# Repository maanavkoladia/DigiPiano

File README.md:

# DigiPiano

The **DigiPiano** is a velocity-sensitive digital piano designed using **STM32** and **ESP32** microcontrollers. It combines advanced sensor technology, high-quality audio playback, and Bluetooth connectivity to deliver a realistic and modern musical experience.

## Project Overview

- **Key Tracking Mechanism:**
  - Uses **Hall effect sensors** and magnets to detect key presses and releases.
  - Tracks key velocity to simulate the dynamics of a real piano.

- **Audio Playback:**
  - Plays pre-recorded piano note samples stored in external memory.
  - Outputs sound via AUX to speakers or streams wirelessly over Bluetooth.

- **Custom Sustain Circuitry:**
  - Includes a custom-designed sustain circuit to enhance the playing experience.

- **Communication Between Microcontrollers:**
  - The STM32 and ESP32 communicate efficiently using **SPI** and **UART** protocols, enabling seamless data exchange for key detection and audio output.

## Implementation Highlights

- The firmware handles multichannel analog data acquisition and processes it to detect key strokes with precision.
- Audio playback is managed through external memory, ensuring low-latency performance.
- Bluetooth functionality allows for wireless connectivity, enabling modern use cases such as streaming to Bluetooth speakers or devices.
- The hardware design incorporates a custom PCB layout for compactness and reliability, integrating sensors, microcontrollers, and audio components.

## See It in Action

Check out this [Instagram reel](https://www.instagram.com/reel/DDNmyurpquJ/?igsh=Y2NvNWVrb3MxazM1) to see the DigiPiano in action!

The DigiPiano is a versatile and user-friendly project, blending traditional piano functionality with modern digital and IoT capabilities.

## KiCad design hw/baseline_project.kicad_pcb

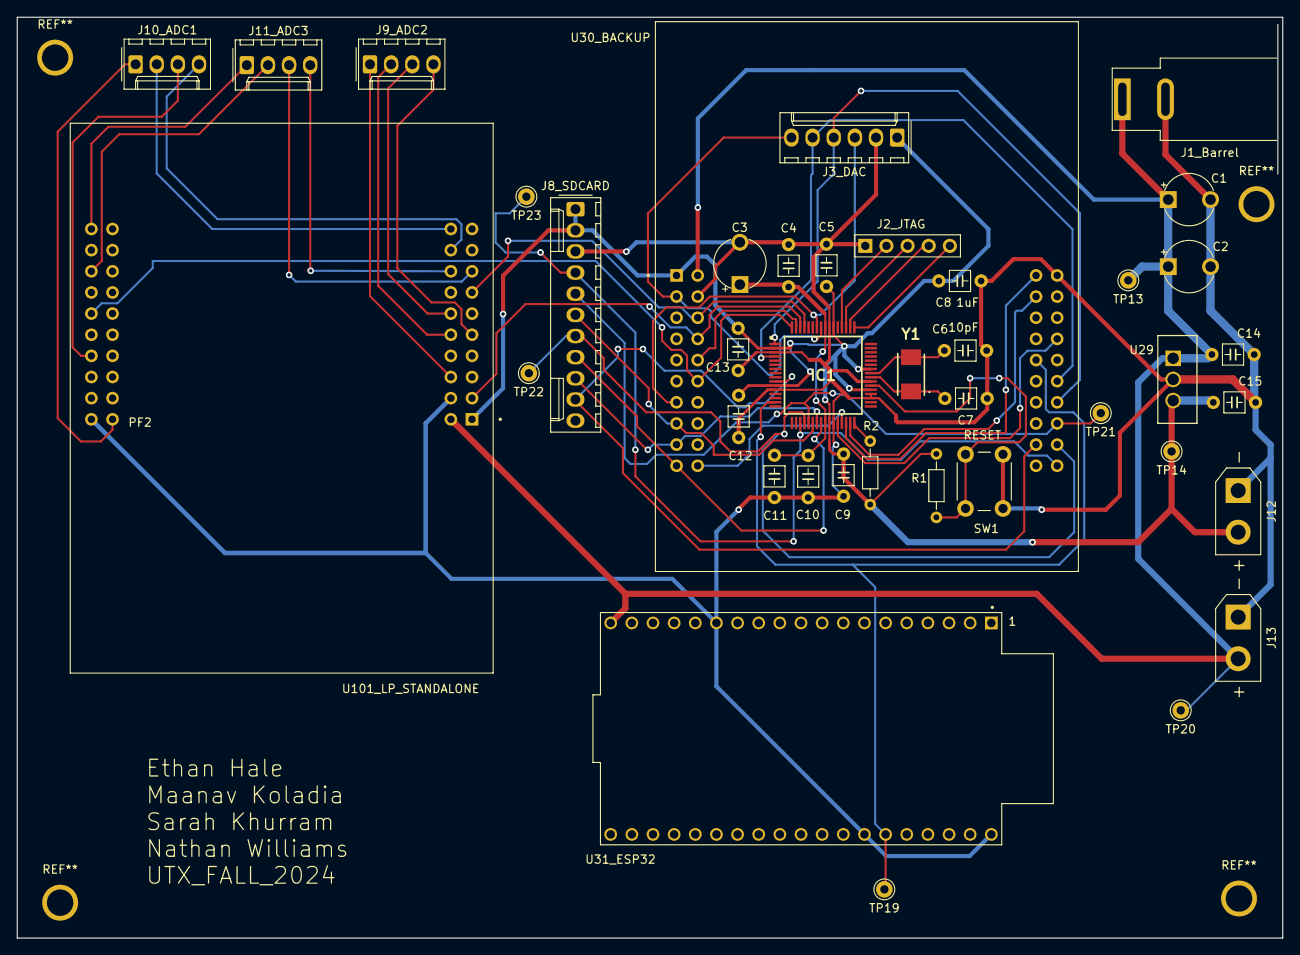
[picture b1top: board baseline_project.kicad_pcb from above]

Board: 2 copper layers, 152.0 x 110.6 mm, 40 parts (0 on the bottom side), 44 nets.

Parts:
C1, C2: 1uF; CP_Radial_Tantal200mil
C3: 2.2uF; CP_Radial_Tantal200mil
C4, C5, C10, C12, C14: 0.1uF; C_Axial_200mil
C6, C7: 10pF; C_Axial_200mil
C8, C11: 1uF; C_Axial_200mil
C9, C13: 0.01uF; C_Axial_200mil
C15: 10uF; C_Axial_200mil
IC1: TM4C123GH6PMIR; QFP50P1200X1200X160-64N
J1_Barrel: Barrel_Jack; BarrelJack_SwitchcraftConxall_RAPC10U_Horizontal
J2_JTAG: Header_5; PinHeader_1x05_P2.54mm_Vertical
J3_DAC: Conn_01x06_Socket_DAC; Molex_KK-254_AE-6410-06A_1x06_P2.54mm_Vertical
J8_SDCARD: LCD SD HEADERS; Molex_KK-254_AE-6410-11A_1x11_P2.54mm_Vertical
J9_ADC2: ADC2; Molex_KK-254_AE-6410-04A_1x04_P2.54mm_Vertical
J10_ADC1: ADC1; Molex_KK-254_AE-6410-04A_1x04_P2.54mm_Vertical
J11_ADC3: ADC3; Molex_KK-254_AE-6410-04A_1x04_P2.54mm_Vertical
J12: 3.3V Pads; AMASS_XT30UPB-M_1x02_P5.0mm_Vertical
J13: 5V Pads; AMASS_XT30UPB-M_1x02_P5.0mm_Vertical
R1: 10k; R_Axial_DIN0204_L3.6mm_D1.6mm_P7.62mm_Horizontal
R2: 1M; R_Axial_DIN0204_L3.6mm_D1.6mm_P7.62mm_Horizontal
SW1: RESET; SW_PUSH_6mm
TP13, TP14, TP19, TP20, TP21, TP22, TP23: TestPoint; Pin_D1.0mm_L10.0mm
U29: LM2937ET-3.3/NOPB; T03B
U30_BACKUP, U101_LP_STANDALONE: EK-TM4C123GXL; ti_EKTM4C123GXL
U31_ESP32: ESP32-DEVKITC; MODULE_ESP32-DEVKITC
Y1: ABM3-16.000MHZ-B2-T; ABM3

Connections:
+3V3: C5.1, C8.1, C9.1, C12.1, C13.1, C15.1, IC1.2 (VDDA), IC1.11 (VDD_1), IC1.26 (VDD_2), IC1.37 (VBAT), IC1.42 (VDD_3), IC1.54 (VDD_4), J3_DAC.1, J8_SDCARD.1, J8_SDCARD.2, J12.2, R1.1, R2.1, TP14.1, U29.3 (OUT), U30_BACKUP.J1_1 (+3.3V), U101_LP_STANDALONE.J1_1 (+3.3V)
+5V: C1.1, C2.1, C14.1, J1_Barrel.1, J13.2, TP13.1, TP20.1, U29.1 (IN), U30_BACKUP.J3_1 (+VBUS), U31_ESP32.19 (EXT_5V), U101_LP_STANDALONE.J3_1 (+VBUS)
/LD0: C3.1, C4.1, C10.1, C11.1, IC1.25 (VDDC_1), IC1.56 (VDDC_2)
GND: C1.2, C2.2, C3.2, C4.2, C5.2, C6.2, C7.1, C8.2, C9.2, C10.2, C11.2, C12.2, C13.2, C14.2, C15.2, IC1.3 (GNDA), IC1.12 (GND_1), IC1.27 (GND_2), IC1.35 (GNDX), IC1.36 (XOSC1), IC1.39 (GND_3), IC1.55 (GND_4), J1_Barrel.2, J2_JTAG.1 (A), J3_DAC.2, J8_SDCARD.3, J12.1, J13.1, SW1.1, U29.2 (GND), U30_BACKUP.J2_1 (GND), U30_BACKUP.J3_2 (GND), U31_ESP32.14 (GND1), U31_ESP32.32 (GND2), U31_ESP32.38 (GND3), U101_LP_STANDALONE.J2_1 (GND), U101_LP_STANDALONE.J3_2 (GND)
IO21: IC1.15 (PC5), TP19.1, U30_BACKUP.J4_5 (PC5), U31_ESP32.33 (IO21)
LP_PA2: J11_ADC3.1, U101_LP_STANDALONE.J2_10 (PA2)
LP_PA4: J11_ADC3.2, U101_LP_STANDALONE.J2_8 (PA4)
LP_PA5: J11_ADC3.3, U101_LP_STANDALONE.J1_8 (PA5)
LP_PB4: IC1.61 (PD0), U30_BACKUP.J3_3 (PD0), U101_LP_STANDALONE.J1_7 (PB4)
LP_PB5: IC1.62 (PD1), U30_BACKUP.J3_4 (PD1), U101_LP_STANDALONE.J1_2 (PB5)
LP_PB7: IC1.64 (PD3), U30_BACKUP.J3_6 (PD3), U101_LP_STANDALONE.J2_6 (PB7)
LP_PD0: J9_ADC2.1, U101_LP_STANDALONE.J3_3 (PD0)
LP_PD2: J9_ADC2.2, U101_LP_STANDALONE.J3_5 (PD2)
LP_PD3: J9_ADC2.3, U101_LP_STANDALONE.J3_6 (PD3)
LP_PE2: J11_ADC3.4, U101_LP_STANDALONE.J3_8 (PE2)
LP_PE3: J10_ADC1.4, U101_LP_STANDALONE.J3_9 (PE3)
LP_PE4: J9_ADC2.4, U101_LP_STANDALONE.J1_5 (PE4)
LP_PF0: J10_ADC1.3, U101_LP_STANDALONE.J2_4 (PF0)
LP_PF1: J10_ADC1.2, U101_LP_STANDALONE.J3_10 (PF1)
LP_PF2: J10_ADC1.1, U101_LP_STANDALONE.J4_1 (PF2)
unnamed: C7.2, IC1.40 (OSC0), Y1.1
unnamed: C6.1, IC1.41 (OSC1), Y1.2
unnamed: IC1.52 (PC0/TCK/SWCLK), J2_JTAG.2 (B)
unnamed: IC1.51 (PC1/TMS/SWDIO), J2_JTAG.3 (C)
unnamed: IC1.50 (PC2/TDI), J2_JTAG.4 (C)
unnamed: IC1.49 (PC3/TDO/SWO), J2_JTAG.5 (C)
unnamed: IC1.38 (~RST), R1.2, SW1.2
unnamed: IC1.32 (~WAKE), R2.2
TM_PA2: IC1.19 (PA2/SSI0C1K), J8_SDCARD.4, TP23.1, U30_BACKUP.J2_10 (PA2)
TM_PA3: IC1.20 (PA3/SSI0FSS), J8_SDCARD.7, TP22.1, U30_BACKUP.J2_9 (PA3)
TM_PA4: IC1.21 (PA4/SSI0RX), J8_SDCARD.5, TP21.1, U30_BACKUP.J2_8 (PA4)
TM_PA5: IC1.22 (PA5/SSI0TX), J8_SDCARD.6, U30_BACKUP.J1_8 (PA5)
TM_PA6: IC1.23 (PA6), J8_SDCARD.9, U30_BACKUP.J1_9 (PA6)
TM_PA7: IC1.24 (PA7), J8_SDCARD.8, U30_BACKUP.J1_10 (PA7)
TM_PB4: IC1.58 (PB4), J3_DAC.3, U30_BACKUP.J1_7 (PB4)
TM_PB5: IC1.57 (PB5), J3_DAC.6, U30_BACKUP.J1_2 (PB5)
TM_PB6: IC1.1 (PB6), J3_DAC.4, U30_BACKUP.J2_7 (PB6)
TM_PB7: IC1.4 (PB7), J3_DAC.5, U30_BACKUP.J2_6 (PB7)
TM_PD2: IC1.63 (PD2), U30_BACKUP.J3_5 (PD2)
TM_PD7: IC1.10 (PD7), J8_SDCARD.10, U30_BACKUP.J4_9 (PD7)
TM_PF0: IC1.28 (PF0), U30_BACKUP.J2_4 (PF0)
TM_PF1: IC1.29 (PF1), U30_BACKUP.J3_10 (PF1)
TM_PF2: IC1.30 (PF2), U30_BACKUP.J4_1 (PF2)
TM_PF3: IC1.31 (PF3), U30_BACKUP.J4_2 (PF3)

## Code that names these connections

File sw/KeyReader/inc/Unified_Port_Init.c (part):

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// Port A drives the ST7735 LCD 
//
// Backlight (pin 10) connected to +3.3 V
// MISO      (pin 9)  connected to PA4
// SCK       (pin 8)  connected to PA2 (SSI0Clk)
// MOSI      (pin 7)  connected to PA5 (SSI0Tx)
// TFT_CS    (pin 6)  connected to PA3 (SSI0Fss)
// CARD_CS   (pin 5)  connected to PB0 (GPIO)
// Data/CMD  (pin 4)  connected to PA6 (GPIO), high for data, low for command
// RESET     (pin 3)  connected to PA7 (GPIO)
// VCC       (pin 2)  connected to +3.3 V
// Gnd       (pin 1)  connected to ground
//
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  SYSCTL_RCGCGPIO_R     |= 0x01;            // Activate port A
  while((SYSCTL_PRGPIO_R & 0x01)==0){};     // allow time for clock to start
    
  GPIO_PORTA_DIR_R      |= 0xC8;            // make PA3,6,7 out
  GPIO_PORTA_AFSEL_R    &= ~0xC8;           // disable alt funct on PA3,6,7
  GPIO_PORTA_DEN_R      |= 0xC8;            // enable digital I/O on PA3,6,7
  
  // configure PA3,6,7 as GPIO
  GPIO_PORTA_PCTL_R      = (GPIO_PORTA_PCTL_R
                         & 0x00FF0FFF)
                         + 0x00000000;
  
  GPIO_PORTA_AMSEL_R    &= ~0xC8;           // disable analog functionality on PA3,6,7

  // initialize SSI0
  GPIO_PORTA_AFSEL_R    |= 0x2C;            // enable alt funct on PA2,3,5
  GPIO_PORTA_DEN_R      |= 0x2C;            // enable digital I/O on PA2,3,5
 
  // configure PA2,3,5 as SSI
  GPIO_PORTA_PCTL_R      = (GPIO_PORTA_PCTL_R
                         & 0xFF0F00FF)
                         + 0x00202200;
  
  GPIO_PORTA_AMSEL_R    &= ~0x2C;           // disable analog functionality on PA2,3,5
  SSI0_CR1_R            &= ~SSI_CR1_SSE;    // disable SSI
  SSI0_CR1_R            &= ~SSI_CR1_MS;     // master mode
  
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// ----------------    PORT B Initialization   --------------------------------
// ----------------------------------------------------------------------------
//
// PB7 = PWM Ouptut to JP6 (M0PWM1)
// PB6 = PWM Output to Motor (M0PWM0)
// PB5 = ADC Input (AIN11)
// PB4 = Timer Capture input (T1CCP0)
// PB3 = GPIO 
// PB2 = GPIO/I2C0
// PB1 = GPIO/I2C0CL
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  SYSCTL_RCGCGPIO_R     |= 0x02;            // activate port B
  while((SYSCTL_PRGPIO_R & 0x02) == 0){};   // Wait
  
  // ---------------  Initialize PB7 as M0PWM1  -----------------------  

  GPIO_PORTB_AFSEL_R    |=  0x80;           // enable alt funct on PB7
  GPIO_PORTB_PCTL_R     &= ~0xF0000000;     // configure PB7 as M0PWM1
  GPIO_PORTB_PCTL_R     |=  0x40000000;
  GPIO_PORTB_AMSEL_R    &= ~0x80;           // disable analog functionality on PB7
  GPIO_PORTB_DEN_R      |=  0x80;           // enable digital I/O on PB7

  // ---------------  Initialize PB6 as M0PWM0  -----------------------
  GPIO_PORTB_AFSEL_R    |=  0x40;           // enable alt funct on PB6
  GPIO_PORTB_PCTL_R     &= ~0x0F000000;     // configure PB6 as PWM0
  GPIO_PORTB_PCTL_R     |=  0x04000000;  
  GPIO_PORTB_AMSEL_R    &= ~0x40;           // disable analog functionality on PB6
  GPIO_PORTB_DEN_R      |=  0x40;           // enable digital I/O on PB6
  
  // ---------------  Initialize PB5 as AIN11  ----------------------- 
  GPIO_PORTB_DIR_R      &= ~0x20;           // make PB5 input
  GPIO_PORTB_AFSEL_R    |=  0x20;           // enable alternate function on PB5
  GPIO_PORTB_DEN_R      &= ~0x20;           // disable digital I/O on PB5
  GPIO_PORTB_AMSEL_R    |=  0x20;           // enable analog functionality on PB5

  // ----------------- Initialize PB4 as Timer Capture input (T1CCP0) ---------
  GPIO_PORTB_DIR_R      &= ~0x10;           // make PB4 input
  GPIO_PORTB_AFSEL_R    |= 0x10;            // enable alt funct on PB4
  GPIO_PORTB_DEN_R      |= 0x10;            // enable digital I/O on PB4
                                            // configure PB4 (T1CCP0)
  GPIO_PORTB_PCTL_R     = (GPIO_PORTB_PCTL_R 
                        &  0xFFF0FFFF)
                        +  0x00070000;
  GPIO_PORTB_AMSEL_R    &= ~0x10;           // disable analog functionality on PB4

  // ----------------- Initialize PB3-0 as GPIO ---------
                                      
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// ----------------------------------------------------------------------------
//
// PC4 = UP switch
// PC5 = RIGHT switch
// PC6 = LEFT switch
// PC7 = DOWN switch
//
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// ----------------    PORT D Initialization   --------------------------------
// ----------------------------------------------------------------------------
//
// PD7 = U2TX
// PD6 = U2RX
// PD3 = SSI1_MOSI  (to TLV5616)
// PD2 = AIN5 (Monitor DAC_OUT signal from TLV5616)
// PD1 = SSI1_FS/CS (to TLV5616)
// PD0 = SSI1_SCK   (to TLV5616)
  
void Port_D_Init(void){
 
  SYSCTL_RCGCGPIO_R     |= 0x08;            // activate port D
  while((SYSCTL_PRGPIO_R & 0x08)==0){};     // allow time for clock to stabilize

  // ---------------  Initialize PB7 as U2TX, PB6 as U2RX  -----------------------  
    
  GPIO_PORTD_LOCK_R      = 0x4C4F434B;      // unlock REQUIRED for PD7
  GPIO_PORTD_CR_R       |= 0xC0;            // commit PD6, PD7
  
  GPIO_PORTD_AMSEL_R    &= ~0xC0;           // disable analog functionality on PD6, PD7
  GPIO_PORTD_AFSEL_R    |=  0xC0;           // enable alternate function on PD6, PD7
  GPIO_PORTD_DEN_R      |=  0xC0;           // enable digital on PD6, PD7 (PD6 is U2RX, PD7 is U2TX)
  GPIO_PORTD_PCTL_R      =(GPIO_PORTD_PCTL_R  
                         & 0x00FFFFFF)
                         | 0x11000000;      // configure PD6, PD7 as UART
 
   // ---------------  Initialize PD2 as AIN5  ----------------------------------  
   
  GPIO_PORTD_DIR_R      &= ~0x04;           // make PD2 input
  GPIO_PORTD_AFSEL_R    |=  0x04;           // enable alternate function on PD2
  GPIO_PORTD_DEN_R      &= ~0x04;           // disable digital I/O on PD2
  GPIO_PORTD_AMSEL_R    |=  0x04;           // enable analog functionality on PD2

  // ---------------  Initialize PD3,1,0 as SSI1 MOSI, FS & SCK  ---------------- 
    
  GPIO_PORTD_AMSEL_R    &= ~0x0B;           // disable analog functionality on PD
  GPIO_PORTD_AFSEL_R    |=  0x0B;           // enable alt funct on PD3,1,0
  GPIO_PORTD_DEN_R      |=  0x0B;           // enable digital I/O on PD3,1,0
  GPIO_PORTD_PCTL_R      = (GPIO_PORTD_PCTL_R
                          & 0xFFFF0F00)
                          + 0x00002022;
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// ----------------------------------------------------------------------------
//
// PE5 = U5TX
// PE4 = U5RX
// PE3 = Heartbeat LED
// PE2 = AIN_1 (DAC_OUT Monitor)
// PE1 = RSTB_8266
// PE0 = 8266_ GPIO_2 

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  SYSCTL_RCGCGPIO_R     |= 0x10;            // activate port E
  while((SYSCTL_PRGPIO_R & 0x10)==0){};

 // ---------------  Initialize PE5 as U5TX, PE4 as U5RX  -----------------------  

  GPIO_PORTE_AFSEL_R    |= 0x30;            // enable alt funct on PE5-4
  GPIO_PORTE_DEN_R      |= 0x30;            // enable digital I/O on PE5-4
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                         + 0x00110000;
  GPIO_PORTE_AMSEL_R    &= ~0x30;           // disable analog functionality on PE

 // ---------------  Initialize PE3,1,0 as GPIO  ---------------------------------  

  GPIO_PORTE_DIR_R      |=  0x0A;           // output digital I/O on PE3,1
  GPIO_PORTE_DIR_R      &= ~0x01;           // input digital I/O on PE0
  GPIO_PORTE_AMSEL_R    &= ~0x0B;           // disable analog functionality on PE3,1,0
  GPIO_PORTE_AFSEL_R    &= ~0x0B;           // disable alt funct on PE3,1,0
  GPIO_PORTE_DEN_R      |=  0x0B;           // enable digital I/O on PE3,1,0
  
  GPIO_PORTE_PCTL_R      = (GPIO_PORTE_PCTL_R 
                         & 0xFFFF0F00);
  
// ---------------  Initialize PE2 as AIN1  ---------------------------------  
  
  GPIO_PORTE_DIR_R      &= ~0x04;           // make PE2 input
  GPIO_PORTE_AFSEL_R    |=  0x04;           // enable alternate function on PE2
  GPIO_PORTE_DEN_R      &= ~0x04;           // disable digital I/O on PE2
  GPIO_PORTE_AMSEL_R    |=  0x04;           // enable analog functionality on PE2
}
  
// ----------------------------------------------------------------------------
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  
  GPIO_PORTF_AMSEL_R    = 0x00;             // disable analog on PF
  GPIO_PORTF_PCTL_R     = 0x00000000;       // PCTL GPIO on PF4-0
  GPIO_PORTF_DIR_R      = 0x0E;             // PF4,PF0 in, PF3-1 out
  GPIO_PORTF_AFSEL_R    = 0x00;             // disable alt funct on PF7-0
  GPIO_PORTF_PUR_R      = 0x11;             // enable pull-up on PF0 and PF4
  GPIO_PORTF_DEN_R      = 0x1F;             // enable digital I/O on PF4-0
}

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
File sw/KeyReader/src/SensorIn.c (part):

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void ADC_IC_Init(void) {
    // Enable SSI0, SSI2, SSI3

    // ---- Configure Port A for SSI0 (PA2-PA5) ----
    // PA2 = SSI0Clk (Clock)
    // PA3 = SSI0Fss (Chip Select/Frame Select, used pe2 instead
    // PA4 = SSI0Rx  (MISO, Master In Slave Out)
    // PA5 = SSI0Tx  (MOSI, Master Out Slave In)

    // ---- Configure Port B for SSI2 (PB4-PB7) ----
    // PB4 = SSI2Clk (Clock)
    // PB5 = SSI2Fss (Chip Select/Frame Select), used pe3 instead
    // PB6 = SSI2Rx  (MISO, Master In Slave Out)
    // PB7 = SSI2Tx  (MOSI, Master Out Slave In)

    // ---- Configure Port D for SSI3 (PD0-PD3) ----
    // PD0 = SSI3Clk (Clock)
    // PD1 = SSI3Fss (Chip Select/Frame Select), using pe4 instead
    // PD2 = SSI3Rx  (MISO, Master In Slave Out)
    // PD3 = SSI3Tx  (MOSI, Master Out Slave In)
    // Enable SSI0, SSI1, SSI2
    SYSCTL_RCGCSSI_R |= (SYSCTL_RCGCSSI_R0 | SYSCTL_RCGCSSI_R2 | SYSCTL_RCGCSSI_R3);  // Enable SSI0, SSI2, and SSI3
    while((SYSCTL_PRSSI_R & (SYSCTL_RCGCSSI_R0 | SYSCTL_RCGCSSI_R2 | SYSCTL_RCGCSSI_R3)) == 0) {}  // Wait until SSI0, SSI2, and SSI3 are ready
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    SYSCTL_RCGCGPIO_R |= (SYSCTL_RCGCGPIO_R0 | SYSCTL_RCGCGPIO_R1 | SYSCTL_RCGCGPIO_R3);  // Enable clocks for Port A, B, D
    while((SYSCTL_PRGPIO_R & (SYSCTL_RCGCGPIO_R0 | SYSCTL_RCGCGPIO_R1 | SYSCTL_RCGCGPIO_R3)) == 0) {}  // Wait until Ports A, B, D are ready

    // ---- Configure Port A for SSI0 (PA2-PA5) ----
    GPIO_PORTA_AFSEL_R |= 0x3C;                    // Enable alt funct on PA2-PA5 
    GPIO_PORTA_DEN_R |= 0x3C;                      // Enable digital I/O on PA2-PA5
    GPIO_PORTA_PCTL_R = (GPIO_PORTA_PCTL_R & 0xFF0000FF) + 0x00222200; // Configure PA2-PA5 as SSI
    GPIO_PORTA_AMSEL_R &= ~0x3C;                  // Disable analog functionality on PA2-PA5
    GPIO_PORTA_DIR_R |= 0x2C;  //make pa2,3,5 out
    GPIO_PORTA_DIR_R &= ~0x10;  //make pa4 in

    // ---- Configure Port B for SSI2 (PB4-PB7) ----
    GPIO_PORTB_AFSEL_R |= 0xF0;                    // Enable alt funct on PB4-PB7
    GPIO_PORTB_DEN_R |= 0xF0;                      // Enable digital I/O on PB4-PB7
    GPIO_PORTB_PCTL_R = (GPIO_PORTB_PCTL_R & 0x0000FFFF) + 0x22220000; // Configure PB4-PB7 as SSI
    GPIO_PORTB_AMSEL_R &= ~0xF0;                   // Disable analog functionality on PB4-PB7
    GPIO_PORTB_DIR_R |= 0xB0;  //make pb 7,5,4 out 11X1XXX
    GPIO_PORTB_DIR_R &= ~0x40;  //make pb6 in   XX0XXXXX
    //GPIO_PORTB_PDR_R |= 0x80;  // Enable pull-down on PB7


    // Set PB7 (SPI2 MOSI) to 8mA drive strength
    //GPIO_PORTB_DR8R_R |= 0x80;  // 0x80 = 0b10000000, enables 8mA drive on PB7


    // ---- Configure Port D for SSI3 (PD0-PD3) ----
    GPIO_PORTD_AFSEL_R |= 0x0F;                    // Enable alt funct on PD0-PD3
    GPIO_PORTD_DEN_R |= 0x0F;                      // Enable digital I/O on PD0-PD3
    GPIO_PORTD_PCTL_R = (GPIO_PORTD_PCTL_R & 0xFFFF0000) + 0x00001111; // Configure PD0-PD3 as SSI
    GPIO_PORTD_AMSEL_R &= ~0x0F;                   // Disable analog functionality on PD0-PD3
    GPIO_PORTD_DIR_R |= 0x0B;  //make pd0,1,4 out XXXX1X11
    GPIO_PORTD_DIR_R &= ~0x04;  //pd2 in XXXXX0XX
    GPIO_PORTD_PUR_R |= 0x08; 
    // ------------------- Configure SSI0 ---------------------
    SSI0_CR1_R = 0x00000000;    // Disable SSI to configure
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    SYSCTL_RCGCGPIO_R |= SYSCTL_RCGCGPIO_R0; // Enable Port A
    while ((SYSCTL_PRGPIO_R & SYSCTL_RCGCGPIO_R0) == 0) {} // Wait until Port A is ready

    // Configure Port A for SSI0 (PA2-PA5)
    GPIO_PORTA_AFSEL_R |= 0x3C;               // Enable alt funct on PA2-PA5
    GPIO_PORTA_DEN_R |= 0x3C;                 // Enable digital I/O on PA2-PA5
    GPIO_PORTA_PCTL_R = (GPIO_PORTA_PCTL_R & 0xFF0000FF) + 0x00222200; // Configure PA2-PA5 as SSI
    GPIO_PORTA_AMSEL_R &= ~0x3C;              // Disable analog functionality on PA2-PA5
    //GPIO_PORTA_DIR_R |= 0x2C;                 // Make PA2, PA3, PA5 output
    //GPIO_PORTA_DIR_R &= ~0x10;                // Make PA4 input (MISO)

    // Configure SSI0
    SSI0_CR1_R = 0x00000000;  // Disable SSI to configure
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    SYSCTL_RCGCGPIO_R |= SYSCTL_RCGCGPIO_R5; // Enable Port F
    while ((SYSCTL_PRGPIO_R & SYSCTL_RCGCGPIO_R5) == 0) {} // Wait until Port F is ready

    // Unlock Port F if necessary (for PF0)
    GPIO_PORTF_LOCK_R = 0x4C4F434B;  // Unlock Port F
    GPIO_PORTF_CR_R = 0x1F;          // Allow changes to PF0-4

    // Configure Port F pins for SSI1 (PF0: SSI1Rx, PF1: SSI1Tx, PF2: SSI1Clk, PF3: SSI1Fss)
    GPIO_PORTF_AFSEL_R |= 0x0F;                 // Enable alternate function on PF0, PF1, PF2, PF3
    GPIO_PORTF_DEN_R |= 0x0F;                   // Enable digital I/O on PF0, PF1, PF2, PF3
    GPIO_PORTF_PCTL_R = (GPIO_PORTF_PCTL_R & 0xFFFF0000) | 0x00002222; // Configure PF0-PF3 as SSI1
    GPIO_PORTF_AMSEL_R &= ~0x0F;                // Disable analog functionality on PF0-PF3
    //GPIO_PORTF_DIR_R |= 0x0A;                   // Make PF1 (Tx) and PF3 (Fss) output
    //GPIO_PORTF_DIR_R &= ~0x05;                  // Make PF0 (Rx) and PF2 (Clk) input

    // Configure SSI1 for SPI Master Mode
    SSI1_CR1_R = 0x00000000;      // Disable SSI1 to configure it as master
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    SYSCTL_RCGCGPIO_R |= SYSCTL_RCGCGPIO_R1; // Enable Port B
    while ((SYSCTL_PRGPIO_R & SYSCTL_RCGCGPIO_R1) == 0) {} // Wait until Port B is ready

    // Configure Port B for SSI2 (PB4-PB7)
    GPIO_PORTB_AFSEL_R |= 0xF0;               // Enable alt funct on PB4-PB7
    GPIO_PORTB_DEN_R |= 0xF0;                 // Enable digital I/O on PB4-PB7
    GPIO_PORTB_PCTL_R = (GPIO_PORTB_PCTL_R & 0x0000FFFF) + 0x22220000; // Configure PB4-PB7 as SSI
    GPIO_PORTB_AMSEL_R &= ~0xF0;              // Disable analog functionality on PB4-PB7
    //GPIO_PORTB_DIR_R |= 0xB0;                 // Make PB4, PB5, PB7 output (PB6 as input)
    // GPIO_PORTB_PDR_R |= 0x80;              // Optional: Enable pull-down on PB7

    // Configure SSI2
    SSI2_CR1_R = 0x00000000;  // Disable SSI to configure
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    SYSCTL_RCGCGPIO_R |= SYSCTL_RCGCGPIO_R3; // Enable Port D
    while ((SYSCTL_PRGPIO_R & SYSCTL_RCGCGPIO_R3) == 0) {} // Wait until Port D is ready

    // Configure Port D for SSI3 (PD0-PD3)
    GPIO_PORTD_AFSEL_R |= 0x0F;               // Enable alt funct on PD0-PD3
    GPIO_PORTD_DEN_R |= 0x0F;                 // Enable digital I/O on PD0-PD3
    GPIO_PORTD_PCTL_R = (GPIO_PORTD_PCTL_R & 0xFFFF0000) + 0x00001111; // Configure PD0-PD3 as SSI
    GPIO_PORTD_AMSEL_R &= ~0x0F;              // Disable analog functionality on PD0-PD3
    //GPIO_PORTD_DIR_R |= 0x0B;                 // Make PD0, PD1, PD3 output, PD2 input
    //GPIO_PORTD_PUR_R |= 0x08;                 // Optional: Enable pull-up on PD3

    // Configure SSI3
    SSI3_CR1_R = 0x00000000;  // Disable SSI to configure
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        
        command = 0x8F | (channel << 4);
        
        GPIO_PORTE_DATA_R &= ~0x04; // PE2 low
        GPIO_PORTE_DATA_R &= ~0x08; // PE3 low
        GPIO_PORTE_DATA_R &= ~0x10; // PE4 low
        
        // Clear receive FIFO
        while (SSI0_SR_R & SSI_SR_RNE) {
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        
        for (volatile uint16_t i = 0; i < CS_DELAY; i++) {}

        GPIO_PORTE_DATA_R |= 0x04; // PE2 on
        GPIO_PORTE_DATA_R |= 0x08; // PE3 on
        GPIO_PORTE_DATA_R |= 0x10; // PE4 on

        while (SSI0_SR_R & SSI_SR_BSY);
        dummy_read = SSI0_DR_R;  // Read and discard dummy data
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    for (int channel = 0; channel < NUMBER_OF_CHANNELS; channel++) {
        command = 0x8F | (2 << 4);

        GPIO_PORTE_DATA_R &= ~0x04;  // PE2 low
        
        // Clear receive FIFO
        while (SSI0_SR_R & SSI_SR_RNE) {
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        
        for(volatile uint16_t i = 0; i < CS_DELAY; i++){}

        GPIO_PORTE_DATA_R |= 0x04;  // PE2 on

        while (SSI0_SR_R & SSI_SR_BSY);
        dummy_read = SSI0_DR_R;  // Read and discard dummy data
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    for (int channel = 0; channel < NUMBER_OF_CHANNELS; channel++) {
        command = 0x8F | (2 << 4);

        GPIO_PORTE_DATA_R &= ~0x08;  // PE3 low (assuming PE3 is the CS for SSI1)
        
        // Clear receive FIFO
        while (SSI1_SR_R & SSI_SR_RNE) {
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        
        for (volatile uint16_t i = 0; i < CS_DELAY; i++) {}

        GPIO_PORTE_DATA_R |= 0x08;  // PE3 on (CS released)

        while (SSI1_SR_R & SSI_SR_BSY);
        dummy_read = SSI1_DR_R;  // Read and discard dummy data
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    for (int channel = 0; channel < NUMBER_OF_CHANNELS; channel++) {
        command = 0x8F | (2 << 4);

        GPIO_PORTE_DATA_R &= ~0x08;  // PE3 low

        // Clear receive FIFO
        while (SSI2_SR_R & SSI_SR_RNE) {
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        
        for(volatile uint16_t i = 0; i < CS_DELAY; i++){}

        GPIO_PORTE_DATA_R |= 0x08;  // PE3 on

        while (SSI2_SR_R & SSI_SR_BSY);
        dummy_read = SSI2_DR_R;  // Read and discard dummy data
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    for (int channel = 0; channel < NUMBER_OF_CHANNELS; channel++) {
        command = 0x8F | (2 << 4);

        GPIO_PORTE_DATA_R &= ~0x10;  // PE4 low

        // Clear receive FIFO
        while (SSI3_SR_R & SSI_SR_RNE) {
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        
        for(volatile uint16_t i = 0; i < CS_DELAY; i++){}

        GPIO_PORTE_DATA_R |= 0x10;  // PE4 on
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
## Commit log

2024-12-07 initial
2024-12-07 added link to ig vid
2024-12-08 added ig link
